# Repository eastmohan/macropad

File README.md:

# macropad
macropad with 6 keys, 1 rotary encoder, 1 0.91" oled, 2 micro eleds

rotary encoder: set to control volume  <br />
keys: mapped to skip/pause songs, turn LEDs and OLED on/off, copy, and paste.  <br />
oled displays current song + artist  <br />
micro eleds and the XIAO onboard LED all cycle a rainbow (synced)  <br />  <br />
to use the oled for now playing, first install rainmeter and then add the skin in this repo. you may need a chrome extension to get now playing info from chrome. it should refresh every few seconds and save the song and artist to a txt file in the rainmeter folder, which the python script reads and prints to the oled.  <br />  <br />
for personal use  <br />
not for commercial use  <br />

**Demo:** https://www.youtube.com/watch?v=B0LNcNpDYtY </br><br>
**Updates since recording:**</br><br>
  Upper left button:
-   On/off button for the LEDs and OLED
-   Upon pressing to turn off, OLED displays a message and LEDs turn off. After a short delay, the OLED powers off as well.
-   When powering on, LEDs turn on immediately and OLED displays a message before going back to song information <br><br>
  OLED:
    Now shows messages for button presses:
-    KEY: Copy
-    KEY: Paste
-    KEY: LEDs ON/OFF
-    KEY: Prev Track
-    KEY: Play/Pause
-  KEY: Next Track

**BOM:** <br />
SK6812MINI-E mini LED - 2 <br />
Resistor_SMD:R_0402_1005Metric <br />
Button_Switch_Keyboard:SW_Cherry_MX_1.00u_PCB - 6 <br />
Keycaps - 6 <br />
Rotary_Encoder:RotaryEncoder_Alps_EC11E-Switch_Vertical_H20mm - 1 <br />
RF_Module:MCU_Seeed_ESP32C3 - 1 <br />
4pinoled:SSD1306-0.91-OLED-4pin-128x32 - 1 <br />
<br />
M3 x 16mm screws - 4 <br/>
M3 heat set inserts - 4 <br/>

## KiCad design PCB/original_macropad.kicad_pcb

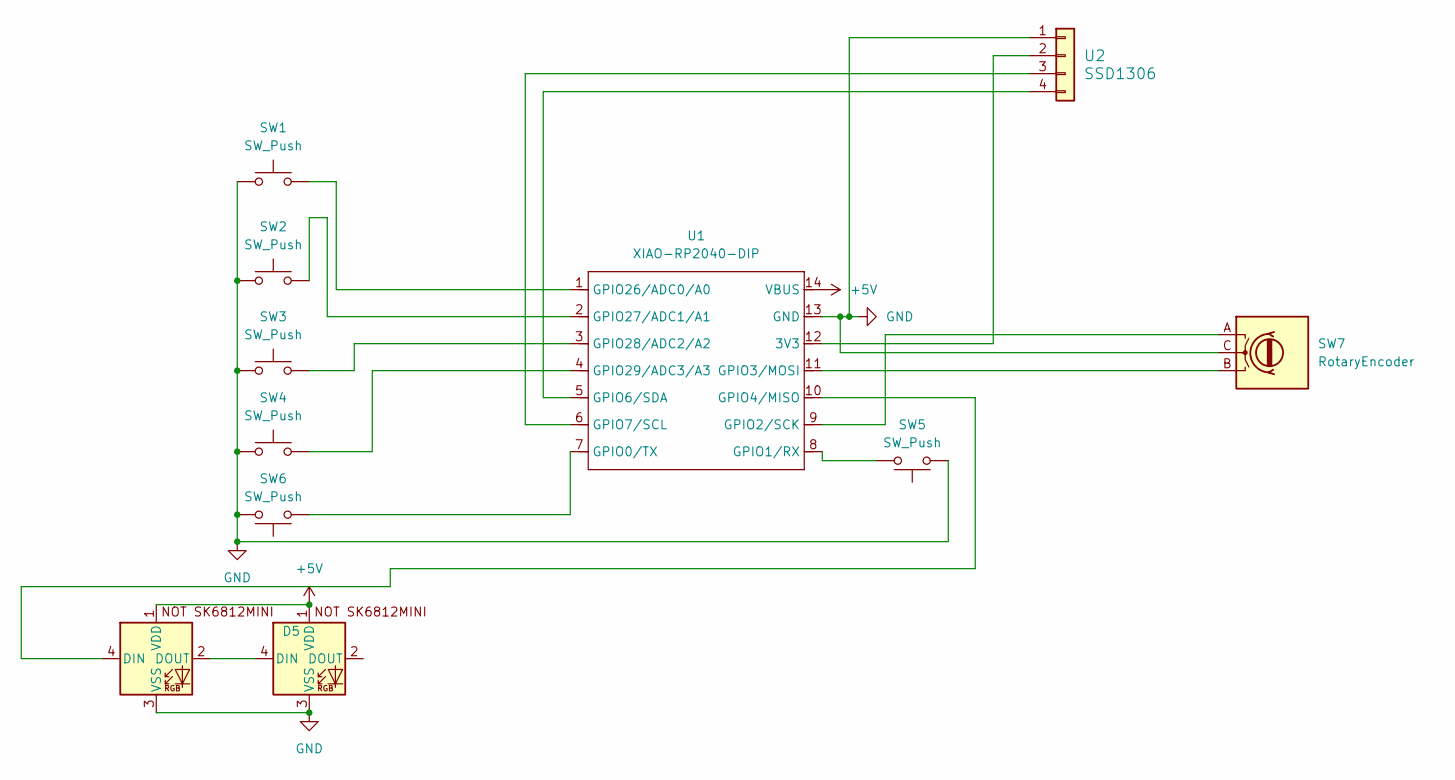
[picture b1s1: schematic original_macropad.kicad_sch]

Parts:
D4, D5: SK6812MINI; SK6812MINI-E_fixed
SW1, SW2, SW3, SW4, SW5, SW6: SW_Push; SW_Cherry_MX_1.00u_PCB
SW7: RotaryEncoder; RotaryEncoder_Alps_EC11E-Switch_Vertical_H20mm
U1: XIAO-RP2040-DIP
U2: SSD1306; SSD1306-0.91-OLED-4pin-128x32

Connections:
+5V: D4.1 (VDD), D5.1 (VDD), U1.14 (VBUS)
GND: D4.3 (VSS), D5.3 (VSS), SW1.1, SW2.1, SW3.1, SW4.1, SW5.1, SW6.2, SW7.C, U1.13 (GND), U2.1
unnamed: D4.4 (DIN), D5.2 (DOUT)
unnamed: D5.4 (DIN), U1.10 (GPIO4/MISO)
unnamed: U1.12 (3V3), U2.2
unnamed: SW6.1, U1.7 (GPIO0/TX)
unnamed: SW5.2, U1.8 (GPIO1/RX)
unnamed: SW7.A, U1.9 (GPIO2/SCK)
unnamed: SW7.B, U1.11 (GPIO3/MOSI)
unnamed: U1.5 (GPIO6/SDA), U2.4
unnamed: U1.6 (GPIO7/SCL), U2.3
unnamed: SW1.2, U1.1 (GPIO26/ADC0/A0)
unnamed: SW2.2, U1.2 (GPIO27/ADC1/A1)
unnamed: SW3.2, U1.3 (GPIO28/ADC2/A2)
unnamed: SW4.2, U1.4 (GPIO29/ADC3/A3)

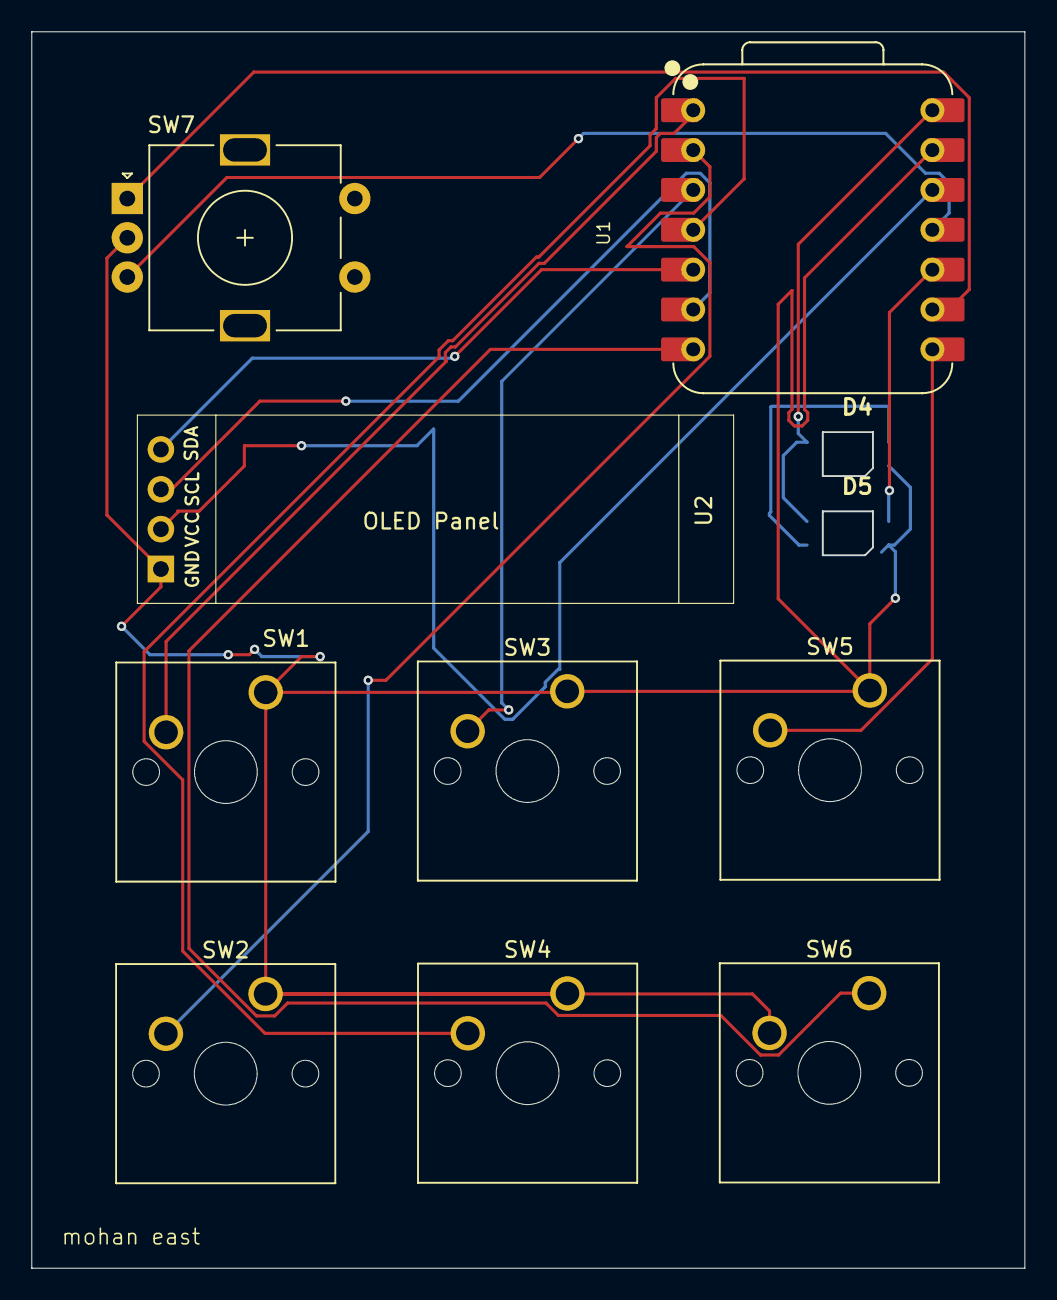
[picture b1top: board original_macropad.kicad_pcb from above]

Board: 2 copper layers, 63.2 x 78.7 mm, 11 parts (0 on the bottom side), 15 nets.

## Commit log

2026-01-28 create pcb folder
2026-01-28 Create firmware folder
2026-01-28 move to folder
2026-02-24 Create txt
2026-02-24 add updated kicad files
2026-03-23 updated cad
2026-03-28 updated firmware
